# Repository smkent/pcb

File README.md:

# PCB designs

A monorepository of my PCB designs created with [KiCAD][kicad] 8.

## Layout and Workflow

Custom symbols and footprints are located in [`libraries`][dir-libraries], which
is shared between PCB projects using [`${KIPRJMOD}`][docs-kiprjmod].

Individual PCB projects (e.g. `*.kicad_pro` and friends) are located within
within [`pcb`][dir-pcb] for active projects, or
[`pcb-archived`][dir-pcb-archived] for archived projects.

When a PCB is ordered from a project, fabrication outputs are created and
in the project's `fab` subdirectory and committed to the repository.

## Setup

Ensure [pipx][pipx] is installed:

```sh
pip install pipx
```

Install [scons][scons]:

```sh
pipx install scons
```

Install KiCAD-related dependencies using the system site packages directory:

```sh
pipx install --system-site-packages kikit interactivehtmlbom
```

## Build

To render all outputs, simply run `scons`.

To render outputs for a particular board, run `scons -u` within that board's
project subdirectory.

## Licenses

Individual hardware designs in this repository may use different licenses.
The following licenses apply unless an included design directory specifies
different license(s).

* Hardware materials and designs are licensed under [CERN Open Hardware License
  version 2.0 Permissive (CERN-OHL-P v2)][license-cern-ohl-p-2.0]
  ([text](/LICENSE.hardware)). The version control history of this repository
  serves as the changes file.
* Software is licensed under the
  [GNU General Public License v3.0 (GPL-3.0)][license-gpl-3.0]
  ([text](/LICENSE.software))
* All documentation is licensed under
  [Creative Commons Attribution-ShareAlike 4.0 International
  (CC-BY-SA-4.0)][license-cc-by-sa-4.0] ([text](/LICENSE.documentation))

The `lcsc` KiCAD [symbols][libraries-lcsc-symbols],
[footprints][libraries-lcsc-pretty], and [3D models][libraries-lcsc-3dshapes]
libraries were created using [easyeda2kicad][easyeda2kicad]
([pypi][easyeda2kicad-pypi]), which are from [LCSC][lcsc]. [More info about
easyeda2kicad][easyeda2kicad-post]

[dir-libraries]: /libraries
[dir-pcb-archived]: /pcb-archived
[dir-pcb]: /pcb
[docs-kiprjmod]: https://docs.kicad.org/8.0/it/pcbnew/pcbnew_footprints_and_libraries.html#fp-path-variable-substitution
[easyeda2kicad-post]: https://hackaday.com/2023/08/08/easyeda2kicad-never-draw-a-footprint-again/
[easyeda2kicad-pypi]: https://pypi.org/project/easyeda2kicad/
[easyeda2kicad]: https://github.com/uPesy/easyeda2kicad.py
[kicad]: https://kicad.org/
[lcsc]: https://lcsc.com
[libraries-lcsc-3dshapes]: /libraries/lcsc.3dshapes
[libraries-lcsc-pretty]: /libraries/lcsc.pretty
[libraries-lcsc-symbols]: /libraries/lcsc.kicad_sym
[license-cc-by-sa-4.0]: https://creativecommons.org/licenses/by-sa/4.0/
[license-cern-ohl-p-2.0]: https://ohwr.org/cern_ohl_p_v2.pdf
[license-gpl-3.0]: https://www.gnu.org/licenses/gpl-3.0.html
[pipx]: https://pipx.pypa.io
[scons]: https://www.scons.org

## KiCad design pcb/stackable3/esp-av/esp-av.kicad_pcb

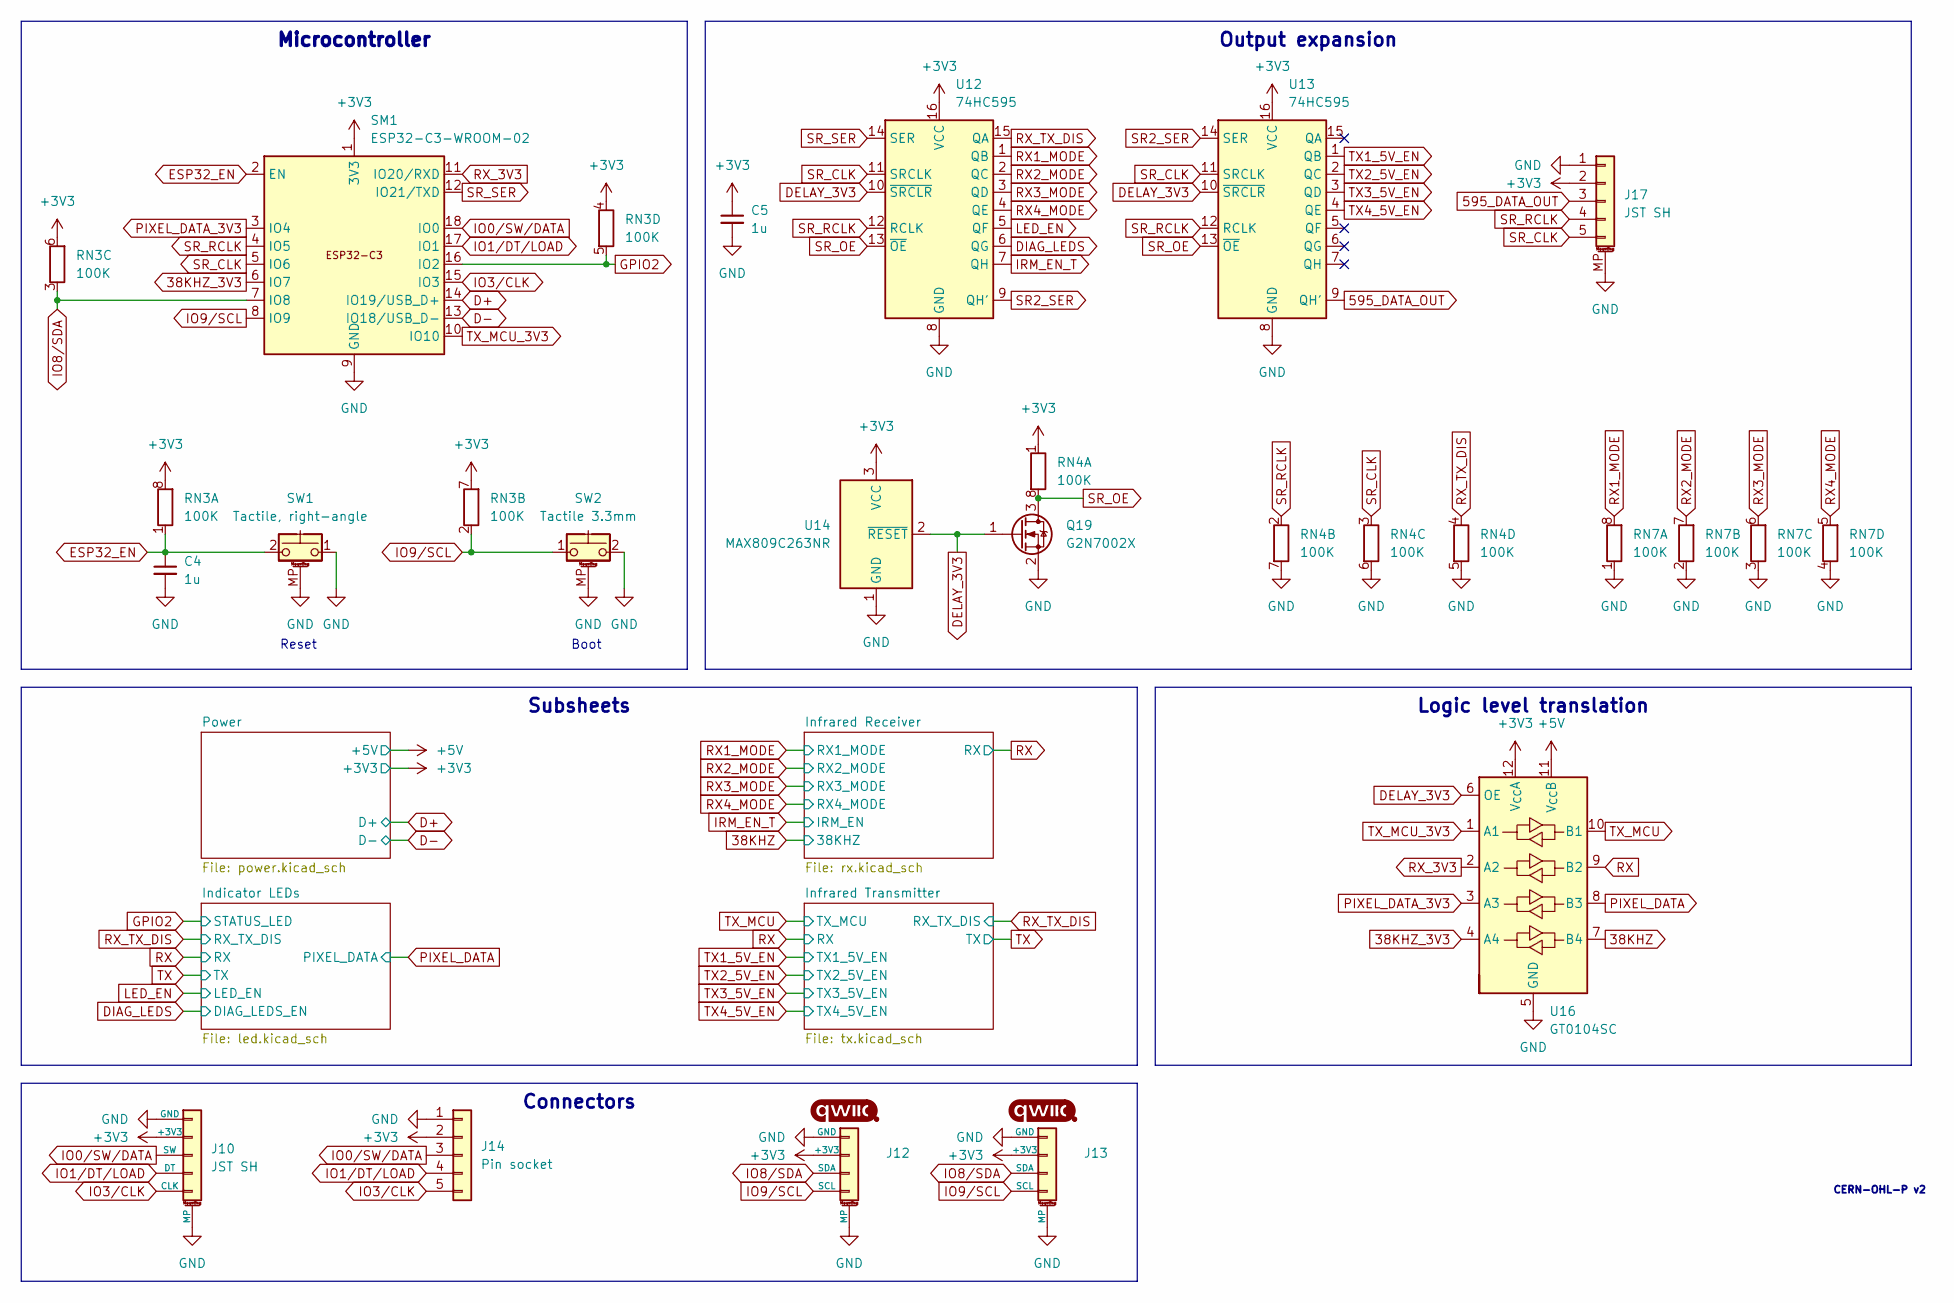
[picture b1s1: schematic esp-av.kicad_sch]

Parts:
C4, C5: 1u; C_0603_1608Metric; LCSC Part C5199872
J10, J17: JST SH; JST_SH_SM05B-SRSS-TB_1x05-1MP_P1.00mm_Horizontal; LCSC Part C7433426
J12: Qwiic; Qwiic-SMD-horizontal-logo-bottom-pinout; LCSC Part C19270571
J13: Qwiic; Qwiic-SMD-vertical; LCSC Part C27636912
J14: Pin socket; PinSocket_1x05_P2.54mm_Vertical
Q19: G2N7002X; SOT-523; LCSC Part C5258971
RN3, RN4, RN7: 100K; R_Array_Convex_4x0603; LCSC Part C110374
SM1: ESP32-C3-WROOM-02
SW1: Tactile, right-angle; SW_Push_1P1T-MP_NO_4.6x3mm_Horizontal; LCSC Part C2888932
SW2: Tactile 3.3mm; SW_Push_1P1T_NO_3.3x3.3mm_MP
U12, U13: 74HC595; SOIC-16_3.9x9.9mm_P1.27mm
U14: MAX809C263NR; SOT-23; LCSC Part C5223646
U16: GT0104SC; QFN-12-1EP_2x2mm_P0.4mm_EP1.1x1.1mm; LCSC Part C22356898

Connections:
38KHZ: U16.7 (B4); also elsewhere on the board
38KHZ_3V3: SM1.6 (IO7), U16.4 (A4)
595_DATA_OUT: J17.3, U13.9 (QH')
+3V3: C5.1, J10.2 (+3V3), J12.2 (+3V3), J13.2 (+3V3), J14.2, J17.2, RN3.4 (R4.1), RN3.6 (R3.2), RN3.7 (R2.2), RN3.8 (R1.2), RN4.1 (R1.1), SM1.1 (3V3), U12.16 (VCC), U13.16 (VCC), U14.3 (VCC), U16.12 (V_{CC}A); also elsewhere on the board
+5V: U16.11 (V_{CC}B); also elsewhere on the board
D+: SM1.14 (IO19/USB_D+); also elsewhere on the board
D-: SM1.13 (IO18/USB_D-); also elsewhere on the board
DELAY_3V3: Q19.1 (G), U12.10 (~SRCLR), U13.10 (~SRCLR), U14.2 (~RESET), U16.6 (OE)
DIAG_LEDS: U12.6 (QG); also elsewhere on the board
ESP32_EN: C4.1, RN3.1 (R1.1), SM1.2 (EN), SW1.2
GND: C4.2, C5.2, J10.1 (GND), J10.MP, J12.1 (GND), J12.MP, J13.1 (GND), J13.MP, J14.1, J17.1, J17.MP (MountPin), Q19.2 (S), RN4.5 (R4.2), RN4.6 (R3.2), RN4.7 (R2.2), RN7.1 (R1.1), RN7.2 (R2.1), RN7.3 (R3.1), RN7.4 (R4.1), SM1.9 (GND), SM1.19 (GND), SW1.1, SW1.MP (MountPin), SW2.2, SW2.MP (MountPin), U12.8 (GND), U13.8 (GND), U14.1 (GND), U16.5 (GND), U16.13 (Pad); also elsewhere on the board
GPIO2: RN3.5 (R4.2), SM1.16 (IO2); also elsewhere on the board
IO0/SW/DATA: J10.3 (SW), J14.3, SM1.18 (IO0)
IO1/DT/LOAD: J10.4 (DT), J14.4, SM1.17 (IO1)
IO3/CLK: J10.5 (CLK), J14.5, SM1.15 (IO3)
IO8/SDA: J12.3 (SDA), J13.3 (SDA), RN3.3 (R3.1), SM1.7 (IO8)
IO9/SCL: J12.4 (SCL), J13.4 (SCL), RN3.2 (R2.1), SM1.8 (IO9), SW2.1
IRM_EN_T: U12.7 (QH); also elsewhere on the board
LED_EN: U12.5 (QF); also elsewhere on the board
PIXEL_DATA: U16.8 (B3); also elsewhere on the board
PIXEL_DATA_3V3: SM1.3 (IO4), U16.3 (A3)
RX: U16.9 (B2); also elsewhere on the board
RX1_MODE: RN7.8 (R1.2), U12.1 (QB); also elsewhere on the board
RX2_MODE: RN7.7 (R2.2), U12.2 (QC); also elsewhere on the board
RX3_MODE: RN7.6 (R3.2), U12.3 (QD); also elsewhere on the board
RX4_MODE: RN7.5 (R4.2), U12.4 (QE); also elsewhere on the board
RX_3V3: SM1.11 (IO20/RXD), U16.2 (A2)
RX_TX_DIS: RN4.4 (R4.1), U12.15 (QA); also elsewhere on the board
SR2_SER: U12.9 (QH'), U13.14 (SER)
SR_CLK: J17.5, RN4.3 (R3.1), SM1.5 (IO6), U12.11 (SRCLK), U13.11 (SRCLK)
SR_OE: Q19.3 (D), RN4.8 (R1.2), U12.13 (~OE), U13.13 (~OE)
SR_RCLK: J17.4, RN4.2 (R2.1), SM1.4 (IO5), U12.12 (RCLK), U13.12 (RCLK)
SR_SER: SM1.12 (IO21/TXD), U12.14 (SER)
TX1_5V_EN: U13.1 (QB); also elsewhere on the board
TX2_5V_EN: U13.2 (QC); also elsewhere on the board
TX3_5V_EN: U13.3 (QD); also elsewhere on the board
TX4_5V_EN: U13.4 (QE); also elsewhere on the board
TX_MCU: U16.10 (B1); also elsewhere on the board
TX_MCU_3V3: SM1.10 (IO10), U16.1 (A1)

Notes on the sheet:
Boot
CERN-OHL-P v2
Reset
Connectors
Output expansion
Subsheets
Logic level translation
Microcontroller

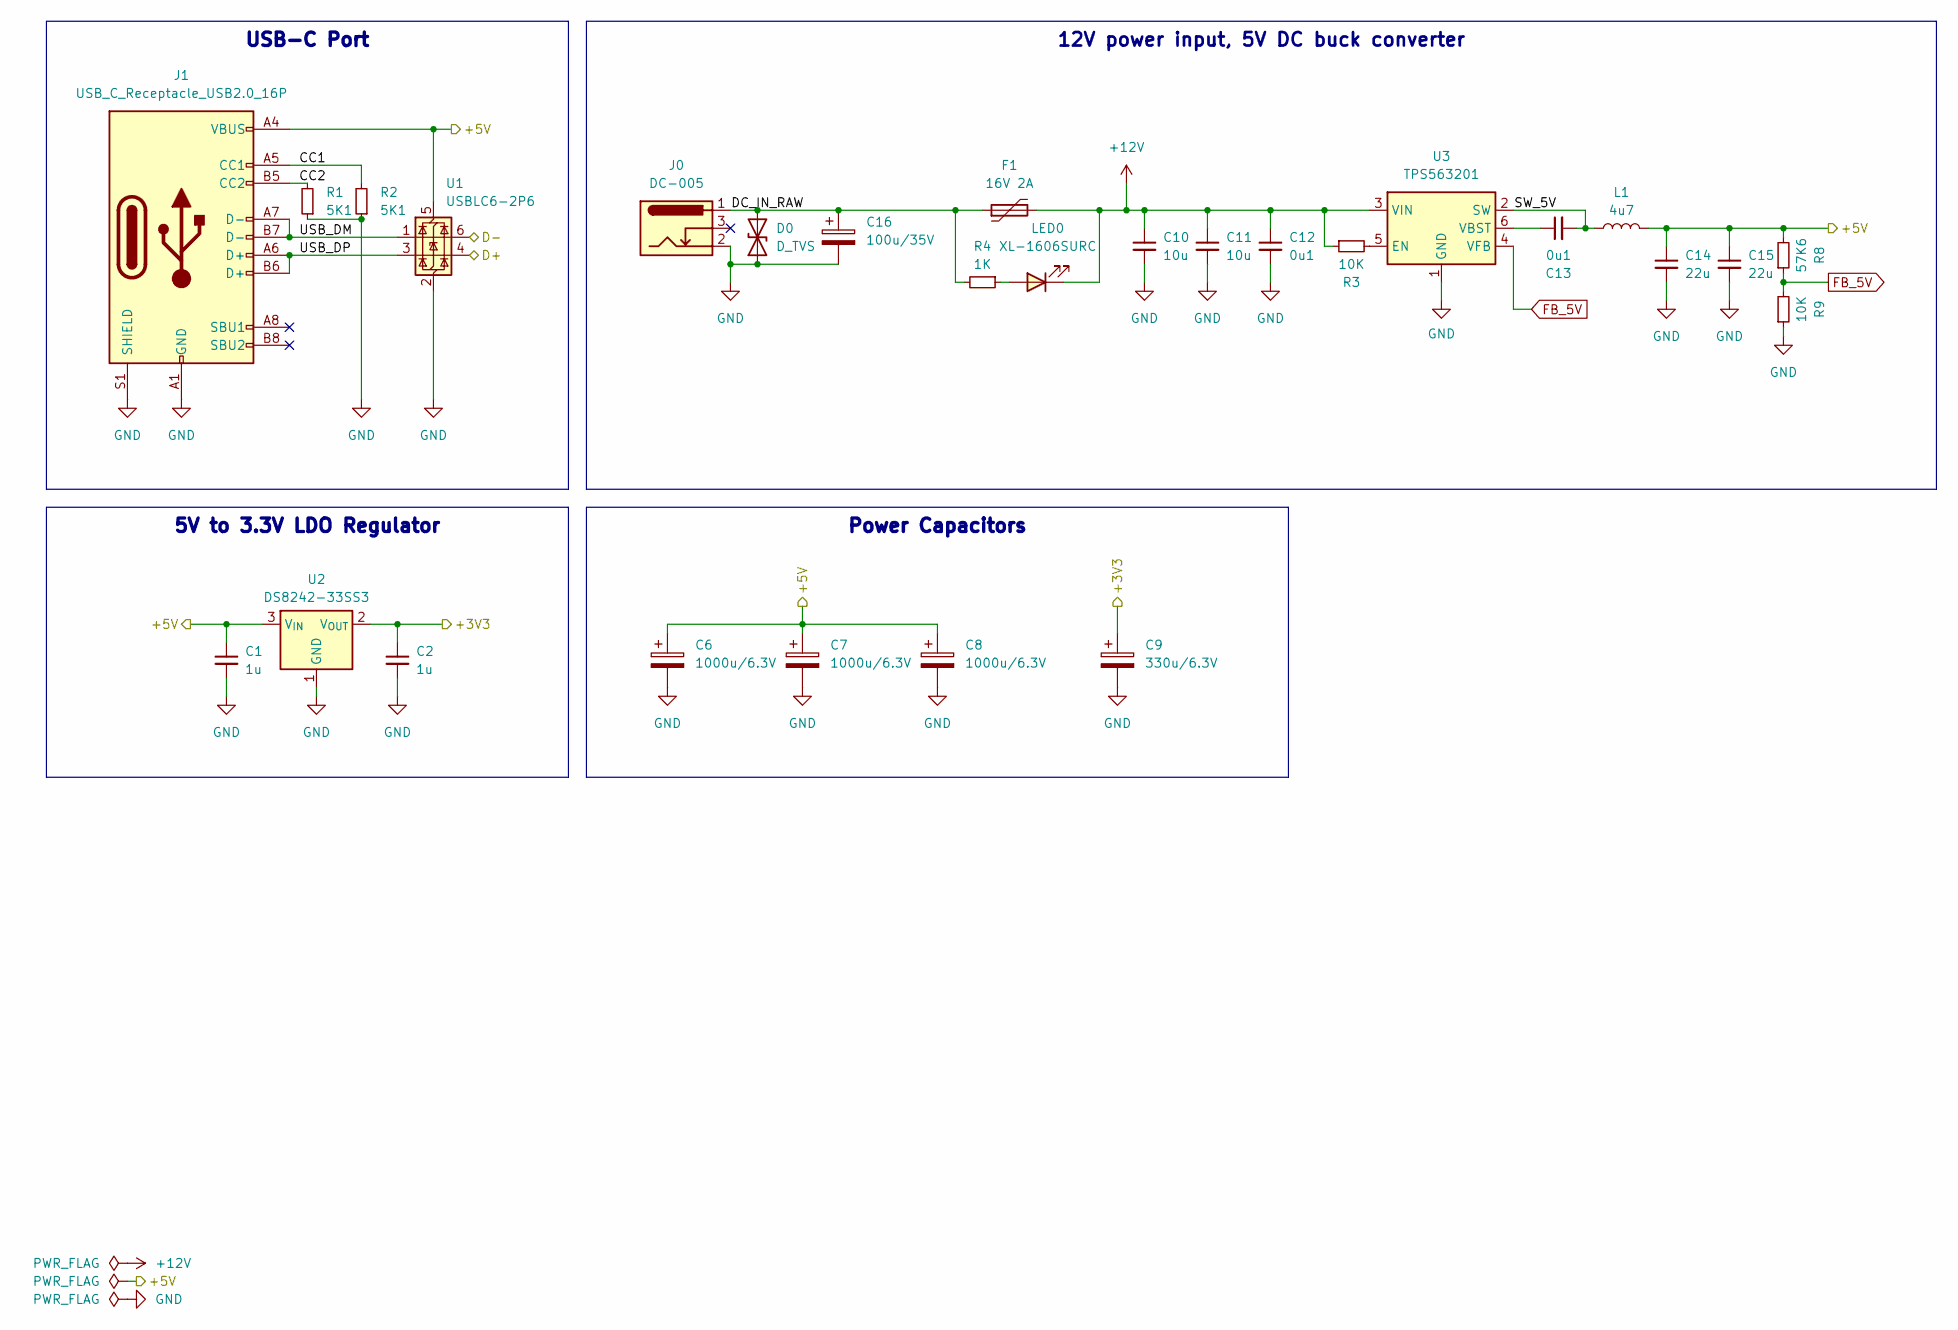
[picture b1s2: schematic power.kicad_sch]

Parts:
C1, C2: 1u; C_0603_1608Metric; LCSC Part C5199872
C6, C7, C8: 1000u/6.3V; CP_Radial_D8.0mm_P3.50mm; LCSC Part C5379966
C9: 330u/6.3V; CP_Radial_D5.0mm_P2.00mm; LCSC Part C217541
C10, C11: 10u; C_0603_1608Metric; LCSC Part C22367825
C12, C13: 0u1; C_0603_1608Metric; LCSC Part C14663
C14, C15: 22u; C_0603_1608Metric; LCSC Part C86295
C16: 100u/35V; CP_Radial_D6.3mm_P2.50mm; LCSC Part C5379947
D0: D_TVS; D_SOD-123F; LCSC Part C7473216
F1: 16V 2A; Fuse_1206_3216Metric; LCSC Part C2982271
J0: DC-005; BarrelJack_DC-005_THT_Horizontal
J1: USB_C_Receptacle_USB2.0_16P; USB_C_Receptacle_GCT_USB4105-xx-A_16P_TopMnt_Horizontal; LCSC Part C2765186
L1: 4u7; L_1008_2520Metric; LCSC Part C22471106
LED0: XL-1606SURC; LED_SideEmitter_1.7x1.1mm; LCSC Part C965860
R1, R2: 5K1; R_0603_1608Metric; LCSC Part C23186
R3, R9: 10K; R_0603_1608Metric; LCSC Part C25804
R4: 1K; R_0603_1608Metric; LCSC Part C21190
R8: 57K6; R_0603_1608Metric; LCSC Part C23082
U1: USBLC6-2P6; SOT-666; LCSC Part C29780639
U2: DS8242-33SS3; SOT-23; LCSC Part C5884134
U3: TPS563201; SOT-23-6; LCSC Part C116592

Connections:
+3V3: C2.1, C9.1, U2.2 (V_{OUT}); also elsewhere on the board
+5V: C1.1, C6.1, C7.1, C8.1, C14.1, C15.1, J1.A4 (VBUS), J1.A9 (VBUS), J1.B4 (VBUS), J1.B9 (VBUS), L1.2, R8.2, U1.5 (VBUS), U2.3 (V_{IN}); also elsewhere on the board
+12V: C10.1, C11.1, C12.1, F1.2, LED0.1 (K), R3.1, U3.3 (VIN)
/Power/CC1: J1.A5 (CC1), R2.2
/Power/CC2: J1.B5 (CC2), R1.2
/Power/DC_IN_RAW: C16.1, D0.2 (A2), F1.1, J0.1, R4.2
/Power/SW_5V: C13.2, L1.1, U3.2 (SW)
/Power/USB_DM: J1.A7 (D-), J1.B7 (D-), U1.1 (I/O1)
/Power/USB_DP: J1.A6 (D+), J1.B6 (D+), U1.3 (I/O2)
D+: U1.4 (I/O2); also elsewhere on the board
D-: U1.6 (I/O1); also elsewhere on the board
FB_5V: R8.1, R9.2, U3.4 (VFB)
GND: C1.2, C2.2, C6.2, C7.2, C8.2, C9.2, C10.2, C11.2, C12.2, C14.2, C15.2, C16.2, D0.1 (A1), J0.2, J1.A1 (GND), J1.A12 (GND), J1.B1 (GND), J1.B12 (GND), J1.S1 (SHIELD), R1.1, R2.1, R9.1, U1.2 (GND), U2.1 (GND), U3.1 (GND); also elsewhere on the board
unnamed: LED0.2 (A), R4.1
unnamed: R3.2, U3.5 (EN)
unnamed: C13.1, U3.6 (VBST)

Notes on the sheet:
12V power input, 5V DC buck converter
Power Capacitors
USB-C Port
5V to 3.3V LDO Regulator

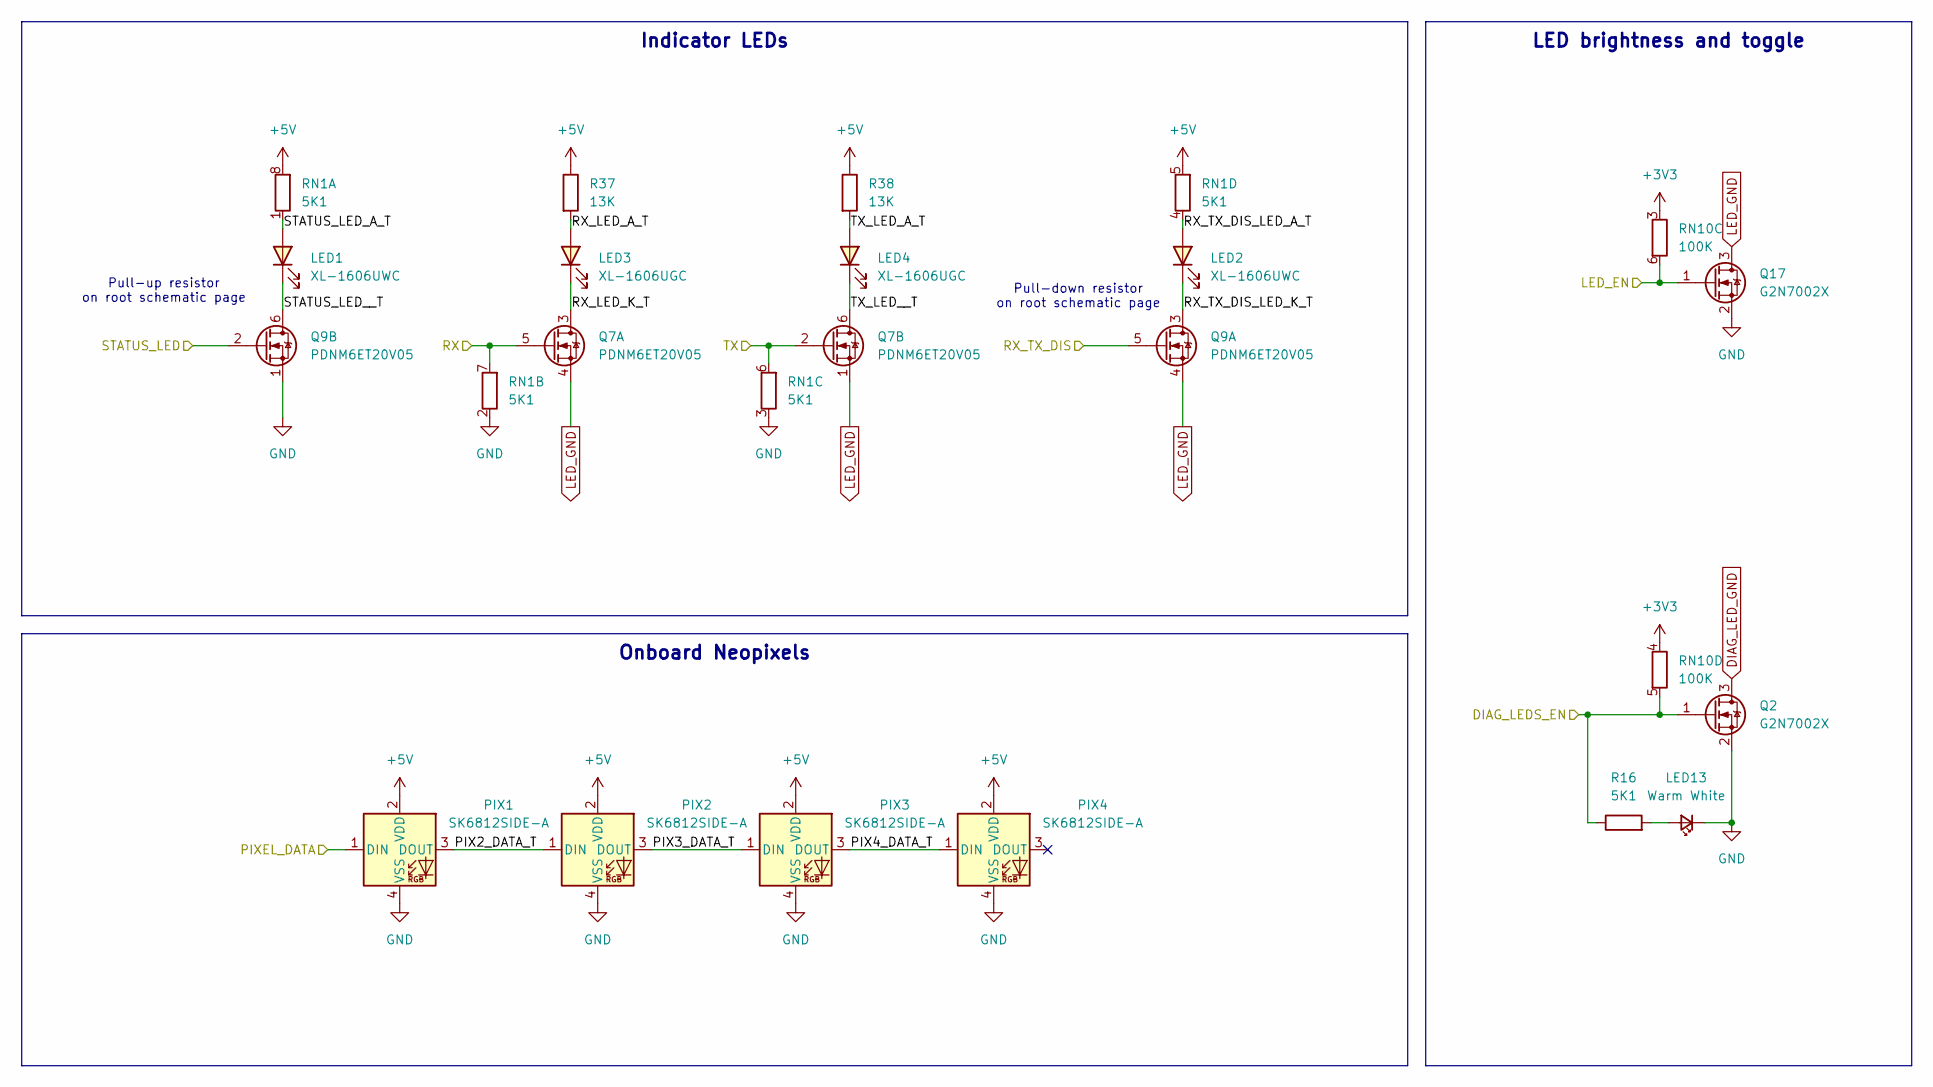
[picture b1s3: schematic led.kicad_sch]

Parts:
LED1, LED2: XL-1606UWC; LED_SideEmitter_1.7x1.1mm; LCSC Part C965866
LED3, LED4: XL-1606UGC; LED_SideEmitter_1.7x1.1mm; LCSC Part C965863
LED13: Warm White; LED_0603_1608Metric; LCSC Part C2827262
PIX1, PIX2, PIX3, PIX4: SK6812SIDE-A; LED_SK6812SIDE-A_4.0x1.6mm; LCSC Part C2890037
Q2, Q17: G2N7002X; SOT-523; LCSC Part C5258971
Q7, Q9: PDNM6ET20V05; SOT-563; LCSC Part C918811
R16: 5K1; R_0603_1608Metric; LCSC Part C23186
R37, R38: 13K; R_0603_1608Metric; LCSC Part C22797
RN1: 5K1; R_Array_Convex_4x0603; LCSC Part C711414
RN10: 100K; R_Array_Convex_4x0603; LCSC Part C110374

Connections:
+3V3: RN10.3 (R3.1), RN10.4 (R4.1); also elsewhere on the board
+5V: PIX1.2 (VDD), PIX2.2 (VDD), PIX3.2 (VDD), PIX4.2 (VDD), R37.1, R38.1, RN1.5 (R4.2), RN1.8 (R1.2); also elsewhere on the board
/Indicator LEDs/PIX2_DATA_T: PIX1.3 (DOUT), PIX2.1 (DIN)
/Indicator LEDs/PIX3_DATA_T: PIX2.3 (DOUT), PIX3.1 (DIN)
/Indicator LEDs/PIX4_DATA_T: PIX3.3 (DOUT), PIX4.1 (DIN)
/Indicator LEDs/RX_LED_A_T: LED3.2 (A), R37.2
/Indicator LEDs/RX_LED_K_T: LED3.1 (K), Q7.3 (D)
/Indicator LEDs/RX_TX_DIS_LED_A_T: LED2.2 (A), RN1.4 (R4.1)
/Indicator LEDs/RX_TX_DIS_LED_K_T: LED2.1 (K), Q9.3 (D)
/Indicator LEDs/STATUS_LED_A_T: LED1.2 (A), RN1.1 (R1.1)
/Indicator LEDs/STATUS_LED__T: LED1.1 (K), Q9.6 (D)
/Indicator LEDs/TX_LED_A_T: LED4.2 (A), R38.2
/Indicator LEDs/TX_LED__T: LED4.1 (K), Q7.6 (D)
DIAG_LEDS: Q2.1 (G), R16.1, RN10.5 (R4.2); also elsewhere on the board
DIAG_LED_GND: Q2.3 (D); also elsewhere on the board
GND: LED13.1 (K), PIX1.4 (VSS), PIX2.4 (VSS), PIX3.4 (VSS), PIX4.4 (VSS), Q2.2 (S), Q9.1 (S), Q17.2 (S), RN1.2 (R2.1), RN1.3 (R3.1); also elsewhere on the board
GPIO2: Q9.2 (G); also elsewhere on the board
LED_EN: Q17.1 (G), RN10.6 (R3.2); also elsewhere on the board
LED_GND: Q7.1 (S), Q7.4 (S), Q9.4 (S), Q17.3 (D)
unnamed: LED13.2 (A), R16.2
PIXEL_DATA: PIX1.1 (DIN); also elsewhere on the board
RX: Q7.5 (G), RN1.7 (R2.2); also elsewhere on the board
RX_TX_DIS: Q9.5 (G); also elsewhere on the board
TX: Q7.2 (G), RN1.6 (R3.2); also elsewhere on the board

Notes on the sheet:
Pull-up resistor on root schematic page
Pull-down resistor on root schematic page
LED brightness and toggle
Onboard Neopixels
Indicator LEDs

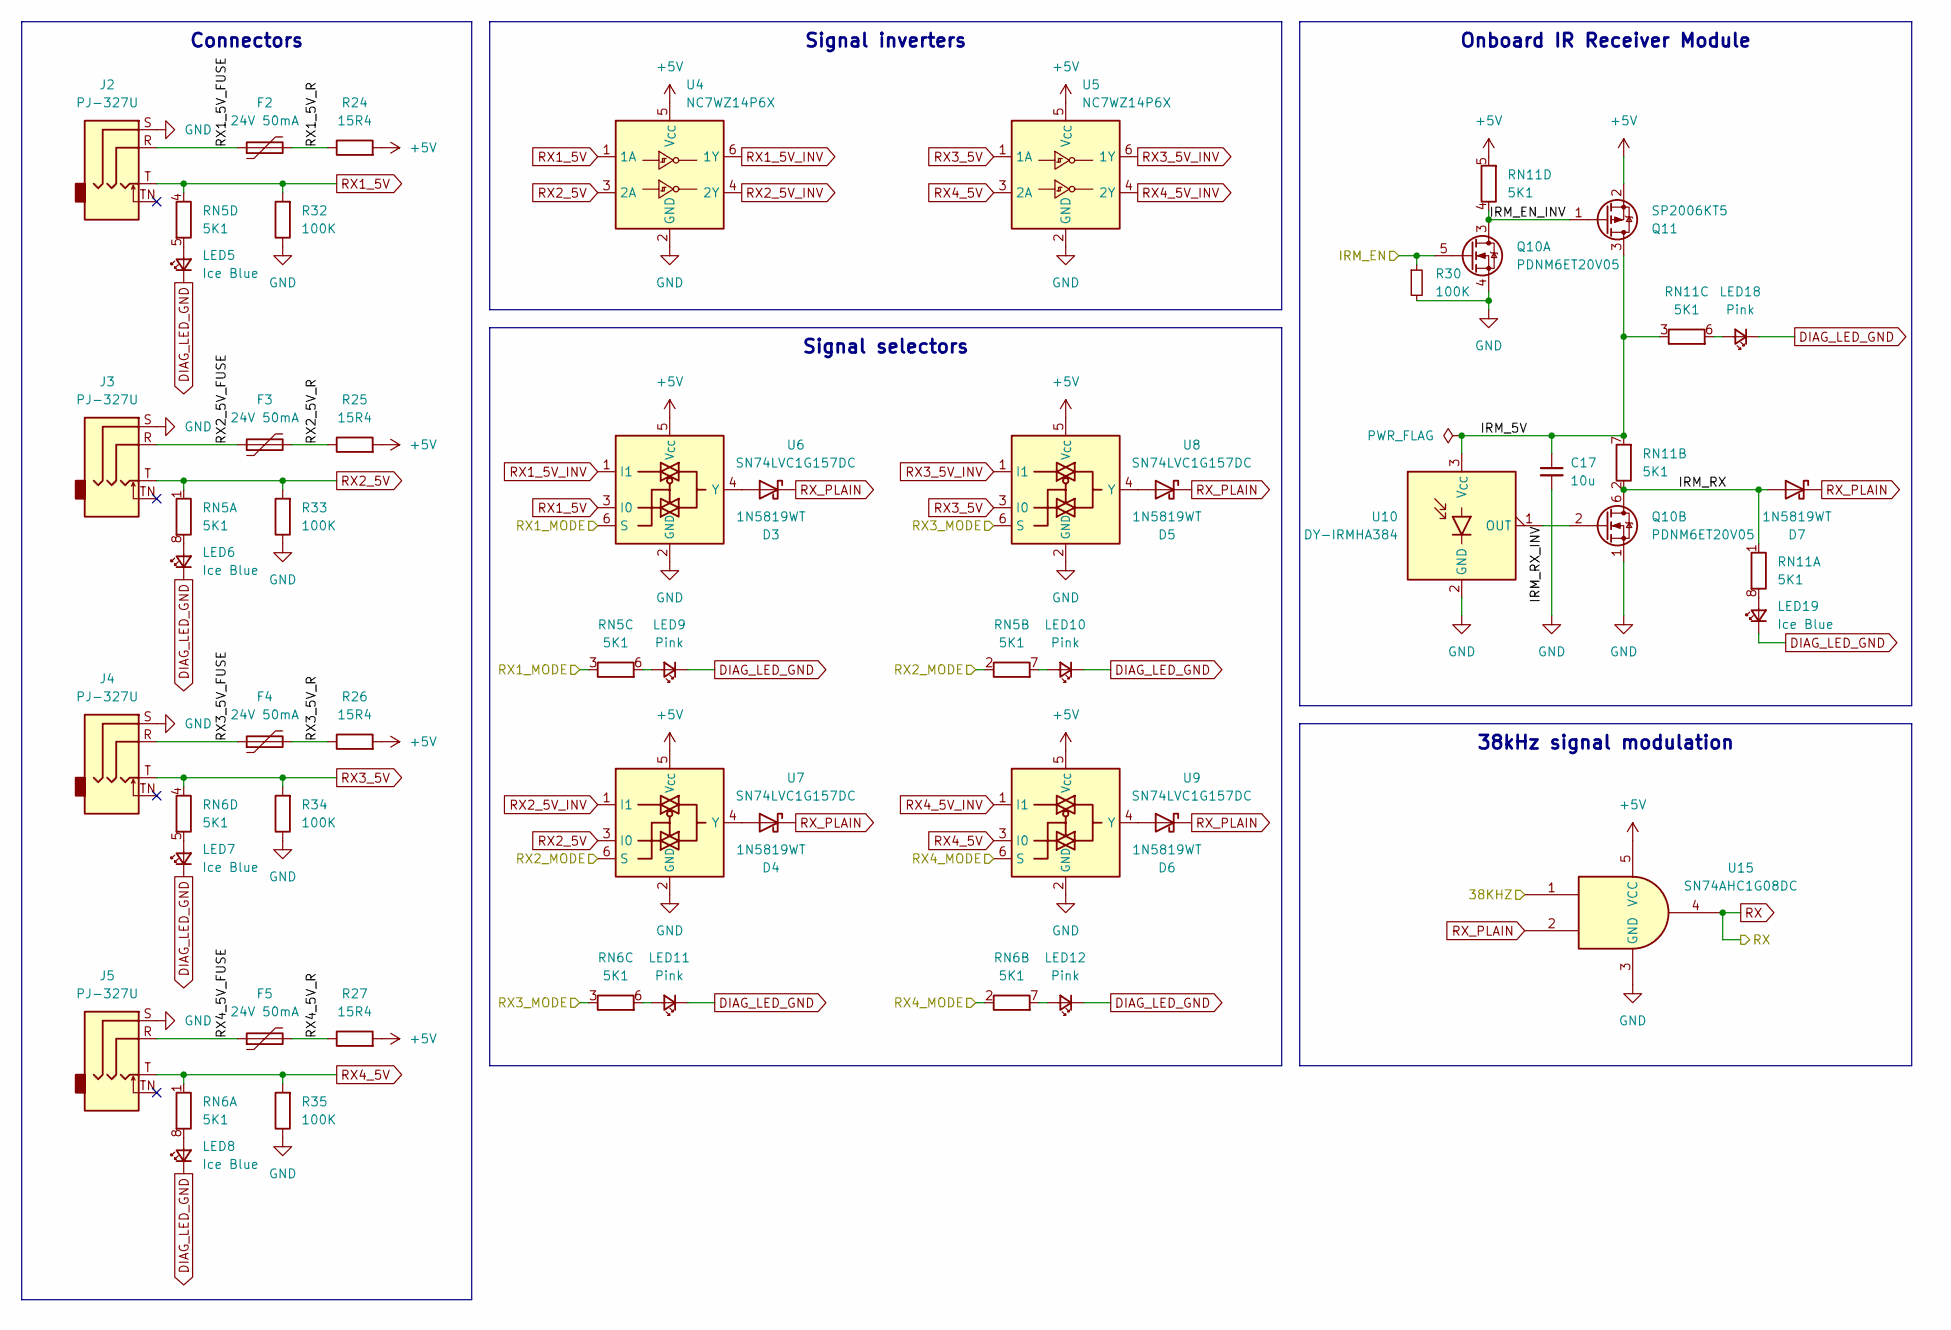
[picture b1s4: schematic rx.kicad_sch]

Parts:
C17: 10u; C_0603_1608Metric; LCSC Part C22367825
D3, D4, D5, D6, D7: 1N5819WT; D_SOD-523; LCSC Part C20754784
F2, F3, F4, F5: 24V 50mA; Fuse_0603_1608Metric; LCSC Part C369141
J2, J3, J4, J5: PJ-327U; Jack_3.5mm_PJ-327U-SMT_Horizontal; LCSC Part C397453
LED5, LED6, LED7, LED8, LED19: Ice Blue; LED_0603_1608Metric; LCSC Part C7496823
LED9, LED10, LED11, LED12, LED18: Pink; LED_0603_1608Metric; LCSC Part C7496826
Q10: PDNM6ET20V05; SOT-563; LCSC Part C918811
Q11: SP2006KT5; SOT-523; LCSC Part C41355141
R24, R25, R26, R27: 15R4; R_1206_3216Metric; LCSC Part C3013373
R30, R32, R33, R34, R35: 100K; R_0603_1608Metric; LCSC Part C25803
RN5, RN6, RN11: 5K1; R_Array_Convex_4x0603; LCSC Part C711414
U4, U5: NC7WZ14P6X; SOT-363_SC-70-6; LCSC Part C5207816
U6, U7, U8, U9: SN74LVC1G157DC; SOT-363_SC-70-6; LCSC Part C22469913
U10: DY-IRMHA384; IRM_5.0mmx4.2mm_P1.27mm_Horizontal; LCSC Part C6071554
U15: SN74AHC1G08DC; SOT-353_SC-70-5; LCSC Part C22469964

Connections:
38KHZ: U15.1; also elsewhere on the board
+5V: Q11.2 (S), R24.2, R25.2, R26.2, R27.2, RN11.5 (R4.2), U4.5 (V_{CC}), U5.5 (V_{CC}), U6.5 (V_{CC}), U7.5 (V_{CC}), U8.5 (V_{CC}), U9.5 (V_{CC}), U15.5 (VCC); also elsewhere on the board
/Infrared Receiver/IRM_5V: C17.1, Q11.3 (D), RN11.3 (R3.1), RN11.7 (R2.2), U10.3 (V_{CC})
/Infrared Receiver/IRM_EN_INV: Q10.3 (D), Q11.1 (G), RN11.4 (R4.1)
/Infrared Receiver/IRM_RX: D7.2 (A), Q10.6 (D), RN11.1 (R1.1), RN11.2 (R2.1)
/Infrared Receiver/IRM_RX_INV: Q10.2 (G), U10.1 (OUT)
/Infrared Receiver/RX1_5V_FUSE: F2.1, J2.R
/Infrared Receiver/RX1_5V_R: F2.2, R24.1
/Infrared Receiver/RX2_5V_FUSE: F3.1, J3.R
/Infrared Receiver/RX2_5V_R: F3.2, R25.1
/Infrared Receiver/RX3_5V_FUSE: F4.1, J4.R
/Infrared Receiver/RX3_5V_R: F4.2, R26.1
/Infrared Receiver/RX4_5V_FUSE: F5.1, J5.R
/Infrared Receiver/RX4_5V_R: F5.2, R27.1
DIAG_LED_GND: LED5.1 (K), LED6.1 (K), LED7.1 (K), LED8.1 (K), LED9.1 (K), LED10.1 (K), LED11.1 (K), LED12.1 (K), LED18.1 (K), LED19.1 (K); also elsewhere on the board
GND: C17.2, J2.S, J3.S, J4.S, J5.S, Q10.1 (S), Q10.4 (S), R30.2, R32.1, R33.1, R34.1, R35.1, U4.2 (GND), U5.2 (GND), U6.2 (GND), U7.2 (GND), U8.2 (GND), U9.2 (GND), U10.2 (GND), U15.3 (GND); also elsewhere on the board
IRM_EN_T: Q10.5 (G), R30.1; also elsewhere on the board
unnamed: D3.2 (A), U6.4 (Y)
unnamed: D4.2 (A), U7.4 (Y)
unnamed: D5.2 (A), U8.4 (Y)
unnamed: D6.2 (A), U9.4 (Y)
unnamed: LED5.2 (A), RN5.5 (R4.2)
unnamed: LED6.2 (A), RN5.8 (R1.2)
unnamed: LED7.2 (A), RN6.5 (R4.2)
unnamed: LED8.2 (A), RN6.8 (R1.2)
unnamed: LED9.2 (A), RN5.6 (R3.2)
unnamed: LED10.2 (A), RN5.7 (R2.2)
unnamed: LED11.2 (A), RN6.6 (R3.2)
unnamed: LED12.2 (A), RN6.7 (R2.2)
unnamed: LED18.2 (A), RN11.6 (R3.2)
unnamed: LED19.2 (A), RN11.8 (R1.2)
RX: U15.4; also elsewhere on the board
RX1_5V: J2.T, R32.2, RN5.4 (R4.1), U4.1 (1A), U6.3 (I0)
RX1_5V_INV: U4.6 (1Y), U6.1 (I1)
RX1_MODE: RN5.3 (R3.1), U6.6 (S); also elsewhere on the board
RX2_5V: J3.T, R33.2, RN5.1 (R1.1), U4.3 (2A), U7.3 (I0)
RX2_5V_INV: U4.4 (2Y), U7.1 (I1)
RX2_MODE: RN5.2 (R2.1), U7.6 (S); also elsewhere on the board
RX3_5V: J4.T, R34.2, RN6.4 (R4.1), U5.1 (1A), U8.3 (I0)
RX3_5V_INV: U5.6 (1Y), U8.1 (I1)
RX3_MODE: RN6.3 (R3.1), U8.6 (S); also elsewhere on the board
RX4_5V: J5.T, R35.2, RN6.1 (R1.1), U5.3 (2A), U9.3 (I0)
RX4_5V_INV: U5.4 (2Y), U9.1 (I1)
RX4_MODE: RN6.2 (R2.1), U9.6 (S); also elsewhere on the board
RX_PLAIN: D3.1 (K), D4.1 (K), D5.1 (K), D6.1 (K), D7.1 (K), U15.2

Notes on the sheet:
Signal inverters
Connectors
Onboard IR Receiver Module
38kHz signal modulation
Signal selectors

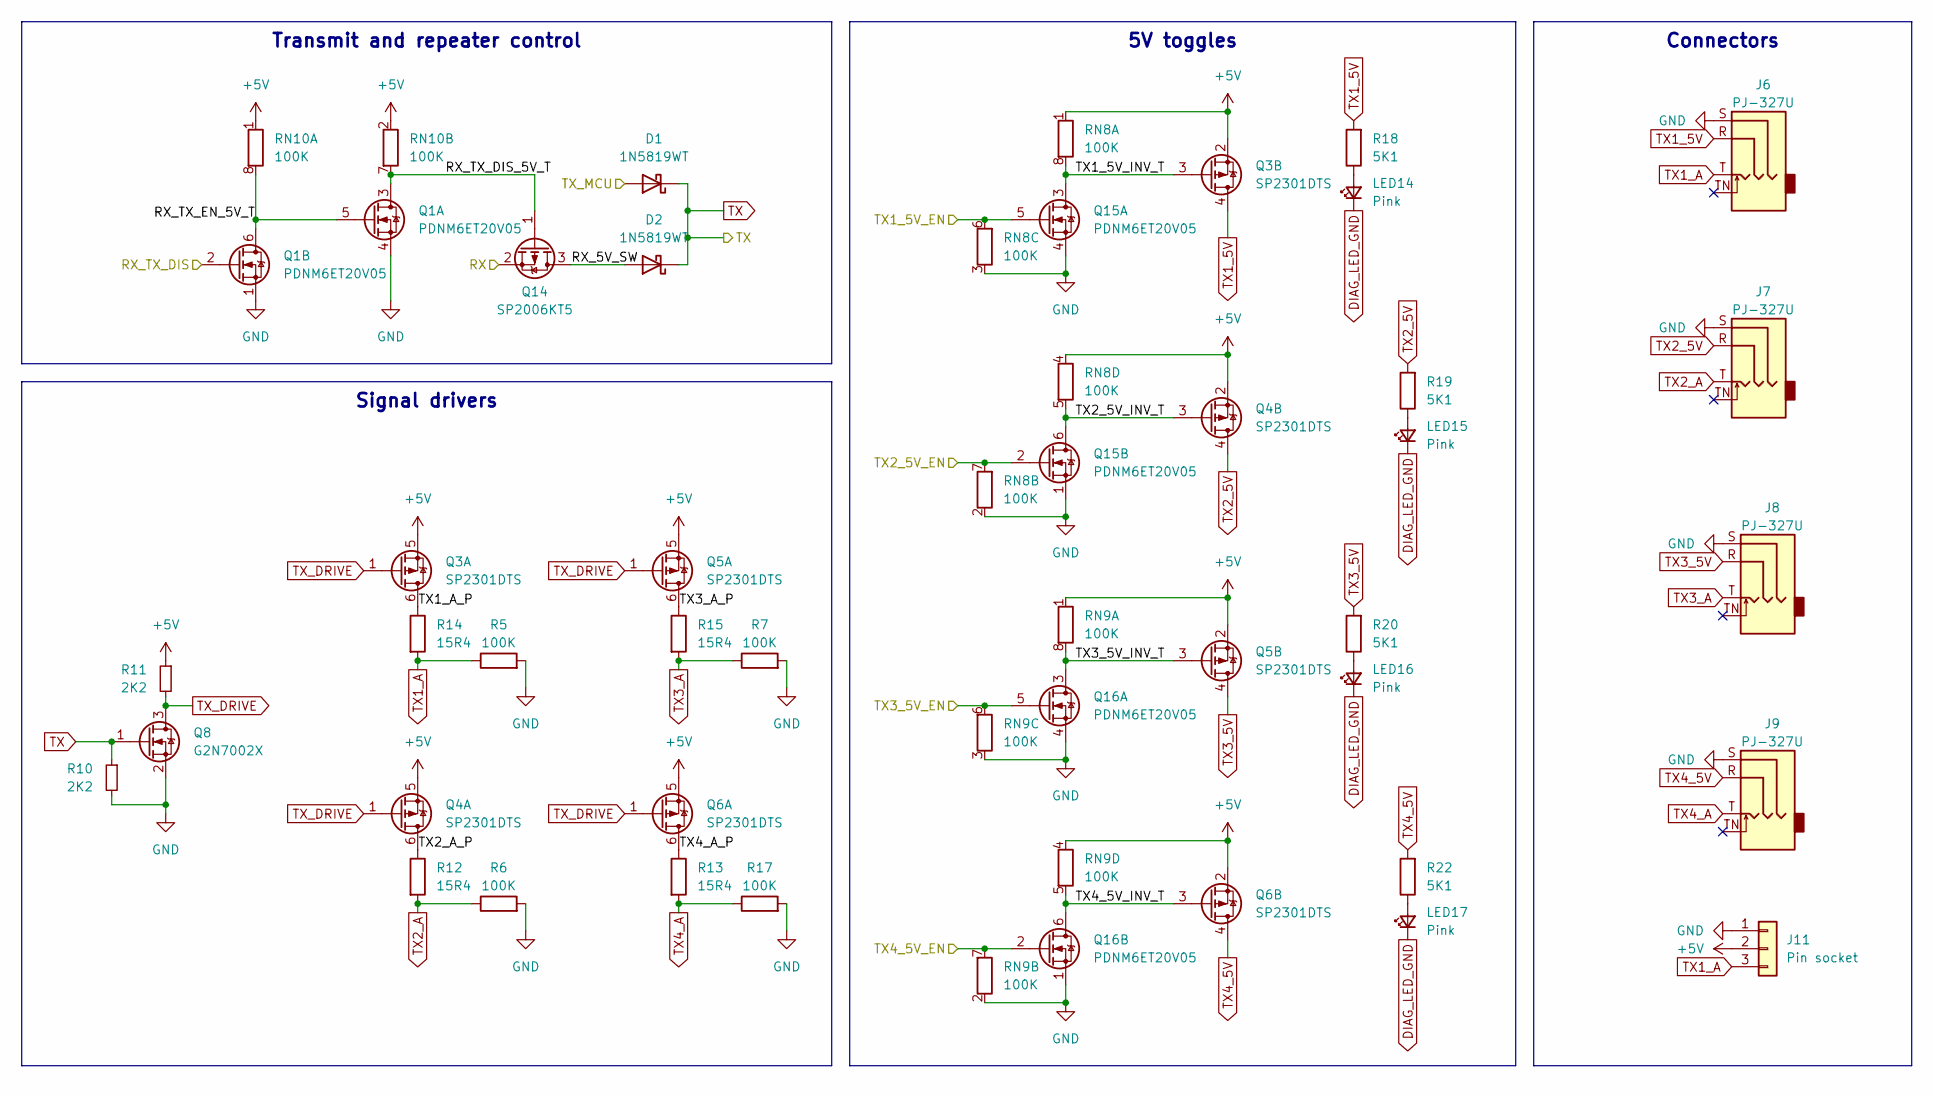
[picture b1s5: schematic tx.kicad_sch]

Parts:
D1, D2: 1N5819WT; D_SOD-523; LCSC Part C20754784
J6, J7, J8, J9: PJ-327U; Jack_3.5mm_PJ-327U-SMT_Horizontal; LCSC Part C397453
J11: Pin socket; PinSocket_1x03_P2.54mm_Vertical
LED14, LED15, LED16, LED17: Pink; LED_0603_1608Metric; LCSC Part C7496826
Q1, Q15, Q16: PDNM6ET20V05; SOT-563; LCSC Part C918811
Q3, Q4, Q5, Q6: SP2301DTS; SOT-23-6; LCSC Part C41355155
Q8: G2N7002X; SOT-523; LCSC Part C5258971
Q14: SP2006KT5; SOT-523; LCSC Part C41355141
R5, R6, R7, R17: 100K; R_0603_1608Metric; LCSC Part C25803
R10, R11: 2K2; R_0603_1608Metric; LCSC Part C4190
R12, R13, R14, R15: 15R4; R_1206_3216Metric; LCSC Part C3013373
R18, R19, R20, R22: 5K1; R_0603_1608Metric; LCSC Part C23186
RN8, RN9, RN10: 100K; R_Array_Convex_4x0603; LCSC Part C110374

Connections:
+5V: J11.2, Q3.2 (S2), Q3.5 (S1), Q4.2 (S2), Q4.5 (S1), Q5.2 (S2), Q5.5 (S1), Q6.2 (S2), Q6.5 (S1), R11.1, RN8.1 (R1.1), RN8.4 (R4.1), RN9.1 (R1.1), RN9.4 (R4.1), RN10.1 (R1.1), RN10.2 (R2.1); also elsewhere on the board
/Infrared Transmitter/RX_5V_SW: D2.2 (A), Q14.3 (D)
/Infrared Transmitter/RX_TX_DIS_5V_T: Q1.3 (D), Q14.1 (G), RN10.7 (R2.2)
/Infrared Transmitter/RX_TX_EN_5V_T: Q1.5 (G), Q1.6 (D), RN10.8 (R1.2)
/Infrared Transmitter/TX1_5V_INV_T: Q3.3 (G2), Q15.3 (D), RN8.8 (R1.2)
/Infrared Transmitter/TX1_A_P: Q3.6 (D1), R14.1
/Infrared Transmitter/TX2_5V_INV_T: Q4.3 (G2), Q15.6 (D), RN8.5 (R4.2)
/Infrared Transmitter/TX2_A_P: Q4.6 (D1), R12.1
/Infrared Transmitter/TX3_5V_INV_T: Q5.3 (G2), Q16.3 (D), RN9.8 (R1.2)
/Infrared Transmitter/TX3_A_P: Q5.6 (D1), R15.1
/Infrared Transmitter/TX4_5V_INV_T: Q6.3 (G2), Q16.6 (D), RN9.5 (R4.2)
/Infrared Transmitter/TX4_A_P: Q6.6 (D1), R13.1
DIAG_LED_GND: LED14.1 (K), LED15.1 (K), LED16.1 (K), LED17.1 (K); also elsewhere on the board
GND: J6.S, J7.S, J8.S, J9.S, J11.1, Q1.1 (S), Q1.4 (S), Q8.2 (S), Q15.1 (S), Q15.4 (S), Q16.1 (S), Q16.4 (S), R5.2, R6.2, R7.2, R10.2, R17.2, RN8.2 (R2.1), RN8.3 (R3.1), RN9.2 (R2.1), RN9.3 (R3.1); also elsewhere on the board
unnamed: LED14.2 (A), R18.1
unnamed: LED15.2 (A), R19.1
unnamed: LED16.2 (A), R20.1
unnamed: LED17.2 (A), R22.1
RX: Q14.2 (S); also elsewhere on the board
RX_TX_DIS: Q1.2 (G); also elsewhere on the board
TX: D1.1 (K), D2.1 (K), Q8.1 (G), R10.1; also elsewhere on the board
TX1_5V: J6.R, Q3.4 (D2), R18.2
TX1_5V_EN: Q15.5 (G), RN8.6 (R3.2); also elsewhere on the board
TX1_A: J6.T, J11.3, R5.1, R14.2
TX2_5V: J7.R, Q4.4 (D2), R19.2
TX2_5V_EN: Q15.2 (G), RN8.7 (R2.2); also elsewhere on the board
TX2_A: J7.T, R6.1, R12.2
TX3_5V: J8.R, Q5.4 (D2), R20.2
TX3_5V_EN: Q16.5 (G), RN9.6 (R3.2); also elsewhere on the board
TX3_A: J8.T, R7.1, R15.2
TX4_5V: J9.R, Q6.4 (D2), R22.2
TX4_5V_EN: Q16.2 (G), RN9.7 (R2.2); also elsewhere on the board
TX4_A: J9.T, R13.2, R17.1
TX_DRIVE: Q3.1 (G1), Q4.1 (G1), Q5.1 (G1), Q6.1 (G1), Q8.3 (D), R11.2
TX_MCU: D1.2 (A); also elsewhere on the board

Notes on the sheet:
Transmit and repeater control
Connectors
5V toggles
Signal drivers
